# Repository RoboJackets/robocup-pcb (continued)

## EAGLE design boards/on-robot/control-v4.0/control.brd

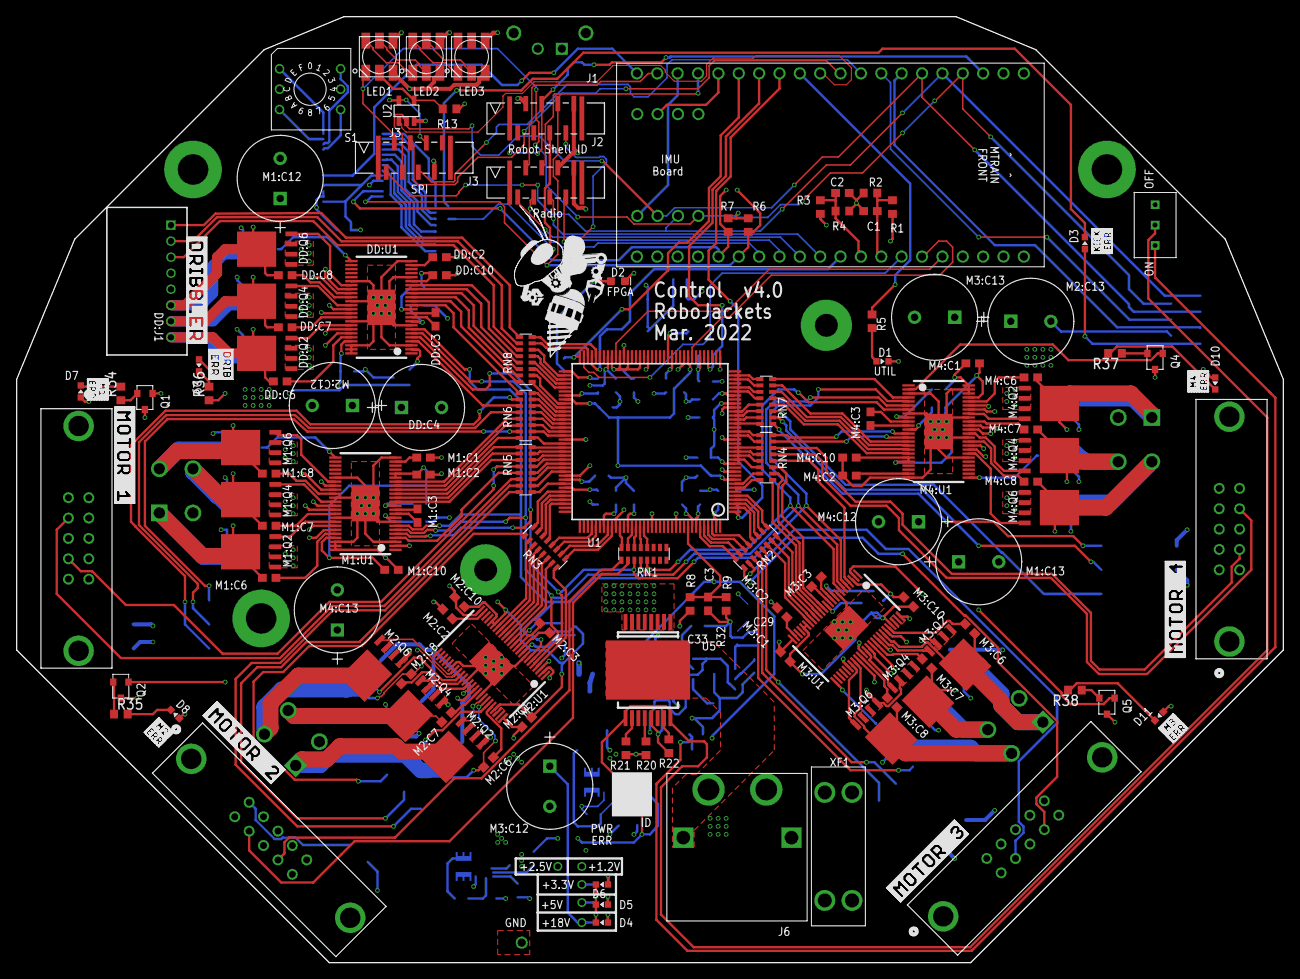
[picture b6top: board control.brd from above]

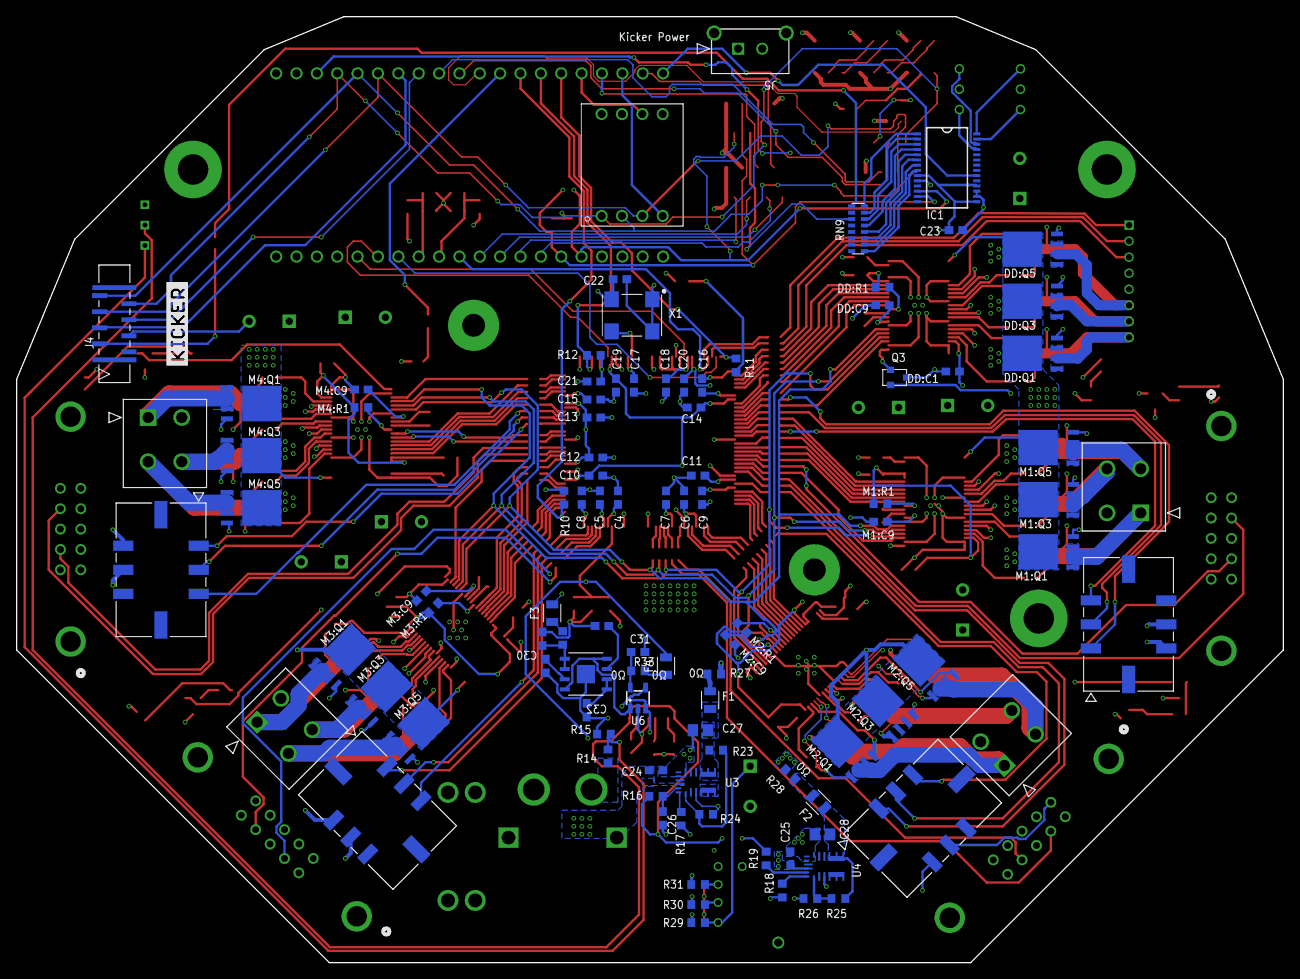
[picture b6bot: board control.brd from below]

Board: 6 copper layers, 158.0 x 118.0 mm, 238 parts (100 on the bottom side), 312 nets.

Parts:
C1: 0.1uF 50V; C0603
C2, C3, C4, C5, C6, C7, C8, C9, C10, C11, C12, C13, C14, C15, C16, C17, C18, C19, C20, C21, C22, C23: 0.1uF; C0603
C24, C25: GRM188R6YA106MA73D; C0603
C26: 2.2uF 50V; C0603
C27, C28: 22uF 16V; C0805
C29: 10uF; C0603
C30, C31, C32, C33: 1uF; C0603
D1: BLUE; CHIP-LED0603
D2: BLUE; LED-0603
D3, D7, D8, D9, D10, D11: RED; CHIP-LED0603
D4, D5, D6: GREEN; CHIP-LED0603
DD:C1, DD:C2: 1uF; C0603
DD:C3: 0.022uF 50V; C0603
DD:C4: ECA-1HHG221; CAP_PAN_10X12.5
DD:C6, DD:C7, DD:C8, DD:C10: 0.1uF 50V; C0603
DD:C9: 2.2uF 50V; C0603
DD:J1: 8-PIN_2MM-H; 2MM-8-H
DD:Q1, DD:Q2, DD:Q3, DD:Q4, DD:Q5, DD:Q6: IRFH7545; PQFN_5X6_E
DD:R1: 10k; R0603
DD:U1: DRV8303DCA; TSSOP-48_PAD
F1, F2, F3, F4: 0805L200SLTHYR; FUSC2113X75
IC1: MCP23017-E/SS; SSOP-28
J1, J2, J3, J4: SFW8S-2STE1LF; CON8_1X8_UB_SFW_JAE
J5: 436500217; CON_436500217_MOL
J6: XT60PW-MAMASS; XT60PW-M
KIT1: MTRAIN; MTRAIN-KIT
KIT2: IMU
LED1, LED2, LED3: APA102C-5050; APA102_5050
M1:C1, M1:C2, M2:C1, M2:C2, M3:C1, M3:C2, M4:C1, M4:C2: 1uF; C0603
M1:C3, M2:C3, M3:C3, M4:C3: 0.022uF 50V; C0603
M1:C6, M1:C7, M1:C8, M1:C10, M2:C6, M2:C7, M2:C8, M2:C10, M3:C6, M3:C7, M3:C8, M3:C10, M4:C6, M4:C7, M4:C8, M4:C10: 0.1uF 50V; C0603
M1:C9, M2:C9, M3:C9, M4:C9: 2.2uF 50V; C0603
M1:C12, M1:C13, M2:C12, M2:C13, M3:C12, M3:C13, M4:C12, M4:C13: ECA-1HHG221; CAP_PAN_10X12.5
M1:J1, M2:J1, M3:J1, M4:J1: 430450618; CON_430450618_MOL
M1:J2, M2:J2, M3:J2, M4:J2: 39288040; CON_39288040
M1:Q1, M1:Q2, M1:Q3, M1:Q4, M1:Q5, M1:Q6, M2:Q1, M2:Q2, M2:Q3, M2:Q4, M2:Q5, M2:Q6, M3:Q1, M3:Q2, M3:Q3, M3:Q4, M3:Q5, M3:Q6, M4:Q1, M4:Q2, M4:Q3, M4:Q4, M4:Q5, M4:Q6: IRFH7545; PQFN_5X6_E
M1:R1, M2:R1, M3:R1, M4:R1: 10k; R0603
M1:U1, M2:U1, M3:U1, M4:U1: DRV8303DCA; TSSOP-48_PAD
M1:U2, M2:U2, M3:U2, M4:U2: N3793-6303RB; N3793-6303RB_3MM
Q1, Q2, Q3, Q4, Q5: PJA3439_R1_00001; SOT-23
R1: 68k 1%; R0603
R2, R3, R4: 10k 1%; R0603
R5, R11: 270; R0603
R6, R7, R10, R12: 4.7k; R0603
R8: 68k; R0603
R9, R20: 10k; R0603
R13: 50k; R0603
R14: 270k; R0603
R15: 100k; R0603
R16, R19: 150k; R0603
R17: 43.2k; R0603
R18: 29.4k; R0603
R21, R22, R29, R30, R31: 1k; R0603
R23, R25: 160k 1%; R0603
R24: 30.1k 1%; R0603
R26: 51.0k 1%; R0603
R27, R28, R32, R33: 0; R0603
R34, R35, R36, R37, R38: 330; R0603
RN1, RN2, RN3, RN4, RN5, RN6, RN7, RN8, RN9: 330; RA-8_2506
S1: 94HCB16T; HEX
S2: TT11EGPC1
U1: XC3S250E-4TQG144C; TQFP144
U2: SN74AHC1G125; SOT-23-5
U3, U4: MPM3620GQV-P
U5: VND5E006ASPTR-E; POWERSO-16
U6: MCP1824T-2502E/OT; SOT-23-5
U7: ADP7158ARDZ-1.2-R7ADP7158ARDZ-1.2-R7_ADI-L; ADP7158ARDZ-1.2-R7_ADI-L
U$1: DRIBBLER
U$2: ERR-KICK
U$3: ERR-DRIB
U$4: ROBOBUZZ_1.0X2
U$5: ERR-M4
U$6: ERR-M1
U$7: MOTOR-1
U$8: MOTOR-4
U$9: MOTOR-2
U$10: ERR-M3
U$11: ERR-M2
U$12: MOTOR-3
U$100: KICKER
X1: ASV-18.432MHZ-EJ-T; ASV
XF1: 30A; 3557-2

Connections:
5V-LED: D5.A, R30.2
5V-LED1: D6.A, R31.2
18.5V-LED: D4.A, R29.1
!CS!-DOT: KIT1.P$11, U2.1
!CS!-FPGA: KIT1.P$31, U1.69
!CS!-ICM: KIT1.P$18, KIT2.4
!CS!-IR: J3.4, KIT1.P$10
!CS!-KICK: J4.5, KIT1.P$8
!CS!-RAD0: J2.4, KIT1.P$17
!RST!-I2C: J1.5, RN9.11
!RST!-IR: J3.5, KIT1.P$9
!RST!-KICK: J4.4, KIT1.P$7
!RST!-RADIO: J2.2, KIT1.P$19
+1.2V: C6.1, C10.1, C14.1, C19.1, F3.2, U1.9, U1.45, U1.80, U1.115
+1.2V-PRE: C29.1, R32.1, U7.1, U7.2
+2.5V: C4.1, C9.1, C15.1, C20.1, F4.2, R10.2, U1.30, U1.65, U1.102, U1.137
+2.5V-PRE: C31.1, R33.1, U6.5
+3.3V: C5.1, C7.1, C8.1, C11.1, C12.1, C13.1, C16.1, C17.1, C18.1, C21.1, C22.1, C23.1, D3.A, D7.A, D8.A, D9.A, D10.A, D11.A, DD:C1.1, DD:C10.1, DD:R1.1, DD:U1.19, DD:U1.45, IC1.9, IC1.15, IC1.18, J3.6, J4.2, KIT2.8, R6.2, R7.2, R12.1, R28.2, R31.1, U1.13, U1.28, U1.42, U1.49, U1.57, U1.60, U1.62, U1.64, U1.79, U1.100, U1.121, U1.138, U1.143, U2.5, U6.1, U6.3, U7.4, U7.8, X1.1, X1.4
+3.3V-FUSE: C28.1, F2.1, R25.2, U4.789
+5V: DD:J1.5, J1.8, J2.6, KIT1.VIN, LED1.1, LED2.1, LED3.1, M1:J1.5, M1:U2.9, M2:J1.5, M2:U2.9, M3:J1.5, M3:U2.9, M4:J1.5, M4:U2.9, R3.1, R27.2, R30.1
+5V-FUSE: C27.1, F1.1, R23.2, U3.789
+18.5V: C24.1, C25.1, DD:C4.1, DD:Q1.5678, DD:Q3.5678, DD:Q5.5678, DD:U1.25, M1:C12.1, M1:C13.1, M1:Q1.5678, M1:Q3.5678, M1:Q5.5678, M1:U1.25, M2:C12.1, M2:C13.1, M2:Q1.5678, M2:Q3.5678, M2:Q5.5678, M2:U1.25, M3:C12.1, M3:C13.1, M3:Q1.5678, M3:Q3.5678, M3:Q5.5678, M3:U1.25, M4:C12.1, M4:C13.1, M4:Q1.5678, M4:Q3.5678, M4:Q5.5678, M4:U1.25, R1.1, R8.1, R29.2, U3.16, U4.16, XF1.3, XF1.4
AAM: R17.2, U3.18
AAM1: R18.2, U4.18
BATT-FPGA: C3.1, R8.2, R9.1, U1.136
BYP: C30.1, U7.3
CS1: R21.2, U5.10
CS2: R22.2, U5.15
CS-DIS: R20.2, U5.12
DD-!CS: DD:U1.4, RN6.11
DD-!FAULT!: DD:U1.2, Q3.1
DD-A-H: DD:U1.13, RN6.9
DD-A-L: DD:U1.14, RN8.16
DD-B-H: DD:U1.15, RN8.15
DD-B-L: DD:U1.16, RN8.14
DD-C-H: DD:U1.17, RN8.13
DD-C-L: DD:U1.18, RN8.12
DD-H1: DD:J1.3, RN8.11
DD-H2: DD:J1.2, RN8.10
DD-H3: DD:J1.1, RN8.9
DD:AVDD: DD:C2.1, DD:U1.23
DD:BST-A: DD:C6.1, DD:U1.44
DD:BST-B: DD:C7.1, DD:U1.39
DD:BST-C: DD:C8.1, DD:U1.34
DD:CP1: DD:C3.1, DD:U1.10
DD:CP2: DD:C3.2, DD:U1.11
DD:EN-GATE: DD:R1.2, DD:U1.12
DD:GH-A: DD:Q1.4, DD:U1.43
DD:GH-B: DD:Q3.4, DD:U1.38
DD:GH-C: DD:Q5.4, DD:U1.33
DD:GL-A: DD:Q2.4, DD:U1.41
DD:GL-B: DD:Q4.4, DD:U1.36
DD:GL-C: DD:Q6.4, DD:U1.31
DD:GVDD: DD:C9.1, DD:U1.9
DD:PHASE-A: DD:C6.2, DD:J1.8, DD:Q1.1, DD:Q1.2, DD:Q1.3, DD:Q2.5678, DD:U1.42
DD:PHASE-B: DD:C7.2, DD:J1.7, DD:Q3.1, DD:Q3.2, DD:Q3.3, DD:Q4.5678, DD:U1.37
DD:PHASE-C: DD:C8.2, DD:J1.6, DD:Q5.1, DD:Q5.2, DD:Q5.3, DD:Q6.5678, DD:U1.32
DOT-CLK-1: LED1.5, R13.2, U2.4
DOT-CLK-1-2: LED1.2, LED2.5
DOT-CLK-2-3: LED2.2, LED3.5
DOT-MOSI-1-2: LED1.3, LED2.4
DOT-MOSI-2-3: LED2.3, LED3.4
EN: C26.1, R16.2, U3.17
EN1: R19.2, U4.17
EN-PWR: R16.1, R19.1, S2.3, U5.9, U5.16
EN-PWR-PRE: R14.1, R15.2, S2.2
EXTRA-IND: KIT1.P$12, R5.1
FB: R23.1, R24.2, U3.1
FB1: R25.1, R26.2, U4.1
FPGA-CLK: U1.50, X1.3
FPGA-DONE: KIT1.P$15, R11.1, U1.72
FPGA-INIT: KIT1.P$14, R12.2, U1.40
FPGA-PROG: KIT1.P$13, R10.1, U1.1
GND: C1.2, C2.2, C3.2, C4.2, C5.2, C6.2, C7.2, C8.2, C9.2, C10.2, C11.2, C12.2, C13.2, C14.2, C15.2, C16.2, C17.2, C18.2, C19.2, C20.2, C21.2, C22.2, C23.2, C24.2, C25.2, C26.2, C27.2, C28.2, C29.2, C30.2, C31.2, C32.2, C33.2, D1.C, D2.C, D4.C, D5.C, D6.C, DD:C1.2, DD:C2.2, DD:C4.2, DD:C9.2, DD:C10.2, DD:J1.4, DD:Q2.1, DD:Q2.2, DD:Q2.3, DD:Q4.1, DD:Q4.2, DD:Q4.3, DD:Q6.1, DD:Q6.2, DD:Q6.3, DD:U1.3, DD:U1.8, DD:U1.20, DD:U1.24, DD:U1.30, DD:U1.35, DD:U1.40, DD:U1.46, DD:U1.47, DD:U1.48, DD:U1.PAD, IC1.10, IC1.16, IC1.17, J1.2, J2.8, J3.7, J4.3, J5.2, J6.P$1, J6.P$3, KIT1.GND, KIT2.5, LED1.6, LED2.6, LED3.6, M1:C1.2, M1:C2.2, M1:C9.2, M1:C10.2, M1:C12.2, M1:C13.2, M1:J1.4, M1:Q2.1, M1:Q2.2, M1:Q2.3, M1:Q4.1, M1:Q4.2, M1:Q4.3, M1:Q6.1, M1:Q6.2, M1:Q6.3, M1:U1.3, M1:U1.8, M1:U1.24, M1:U1.30, M1:U1.35, M1:U1.40, M1:U1.46, M1:U1.47, M1:U1.48, M1:U1.PAD, M1:U2.7, M2:C1.2, M2:C2.2, M2:C9.2, M2:C10.2, M2:C12.2, M2:C13.2, M2:J1.4, M2:Q2.1, M2:Q2.2, M2:Q2.3, M2:Q4.1, M2:Q4.2, M2:Q4.3, M2:Q6.1, M2:Q6.2, M2:Q6.3, M2:U1.3, M2:U1.8, M2:U1.24, M2:U1.30, M2:U1.35, M2:U1.40, M2:U1.46, M2:U1.47, M2:U1.48, M2:U1.PAD, M2:U2.7, M3:C1.2, M3:C2.2, M3:C9.2, M3:C10.2, M3:C12.2, M3:C13.2, M3:J1.4, M3:Q2.1, M3:Q2.2, M3:Q2.3, M3:Q4.1, M3:Q4.2, M3:Q4.3, M3:Q6.1, M3:Q6.2, M3:Q6.3, M3:U1.3, M3:U1.8, M3:U1.24, M3:U1.30, M3:U1.35, M3:U1.40, M3:U1.46, M3:U1.47, M3:U1.48, M3:U1.PAD, M3:U2.7, M4:C1.2, M4:C2.2, M4:C9.2, M4:C10.2, M4:C12.2, M4:C13.2, M4:J1.4, M4:Q2.1, M4:Q2.2, M4:Q2.3, M4:Q4.1, M4:Q4.2, M4:Q4.3, M4:Q6.1, M4:Q6.2, M4:Q6.3, M4:U1.3, M4:U1.8, M4:U1.24, M4:U1.30, M4:U1.35, M4:U1.40, M4:U1.46, M4:U1.47, M4:U1.48, M4:U1.PAD, M4:U2.7, Q1.3, Q2.3, Q3.3, Q4.3, Q5.3, R2.2, R4.2, R9.2, R13.1, R15.1, R17.1, R18.1, R20.1, R21.1, R22.1, R24.1, R26.1, S1.C1, S1.C2, S2.1, U1.11, U1.19, U1.27, U1.37, U1.46, U1.55, U1.61, U1.73, U1.90, U1.99, U1.118, U1.127, U1.133, U2.3, U3.3, U3.12, U3.13, U3.14, U4.3, U4.12, U4.13, U4.14, U5.13, U6.2, U7.EPAD, X1.2
GPB0: IC1.1, RN9.8
GPB1: IC1.2, RN9.7
GPB2: IC1.3, RN9.6
GPB3: IC1.4, RN9.5
GPB4: IC1.5, RN9.4
GPB5: IC1.6, RN9.3
GPB6: IC1.7, RN9.2
GPB7: IC1.8, RN9.1
HEX-0: IC1.28, S1.1
HEX-1: IC1.25, S1.2
HEX-2: IC1.27, S1.4
HEX-3: IC1.26, S1.8
INT-I2C: J1.4, KIT1.P$3
INT-ICM: KIT1.P$16, KIT2.6
INT-IO: IC1.20, KIT1.P$20
INT-RAD0: J2.5, KIT1.P$30
LED-DD: D9.C, R36.2
LED-KICK: D3.C, RN9.9
LED-M1: D7.C, R34.2
LED-M2: D8.C, R35.2
LED-M3: D11.C, R38.2
LED-M4: D10.C, R37.2
M1-!CS: M1:U1.4, RN5.13
M1-!FAULT!: M1:U1.2, Q1.1
M1-A-H: M1:U1.15, RN5.9
M1-A-L: M1:U1.16, RN6.16
M1-B-H: M1:U1.13, RN5.11
M1-B-L: M1:U1.14, RN5.10
M1-C-H: M1:U1.17, RN6.14
M1-C-L: M1:U1.18, RN6.13
M1-ENC-A: M1:U2.8, RN5.14
M1-ENC-B: M1:U2.4, RN5.12
M1-H1: M1:J1.1, RN6.10
M1-H2: M1:J1.2, RN6.12
M1-H3: M1:J1.3, RN6.15
M1:+3.3V: M1:C1.1, M1:C10.1, M1:R1.1, M1:U1.19, M1:U1.20, M1:U1.45
M1:AVDD: M1:C2.1, M1:U1.23
M1:BST-A: M1:C6.1, M1:U1.44
M1:BST-B: M1:C7.1, M1:U1.39
M1:BST-C: M1:C8.1, M1:U1.34
M1:CP1: M1:C3.1, M1:U1.10
M1:CP2: M1:C3.2, M1:U1.11
M1:EN-GATE: M1:R1.2, M1:U1.12
M1:GH-A: M1:Q1.4, M1:U1.43
M1:GH-B: M1:Q3.4, M1:U1.38
M1:GH-C: M1:Q5.4, M1:U1.33
M1:GL-A: M1:Q2.4, M1:U1.41
M1:GL-B: M1:Q4.4, M1:U1.36
M1:GL-C: M1:Q6.4, M1:U1.31
M1:GVDD: M1:C9.1, M1:U1.9
M1:PHASE-A: M1:C7.2, M1:J2.4, M1:Q3.1, M1:Q3.2, M1:Q3.3, M1:Q4.5678, M1:U1.37
M1:PHASE-B: M1:C6.2, M1:J2.1, M1:Q1.1, M1:Q1.2, M1:Q1.3, M1:Q2.5678, M1:U1.42
M1:PHASE-C: M1:C8.2, M1:J2.3, M1:Q5.1, M1:Q5.2, M1:Q5.3, M1:Q6.5678, M1:U1.32
M2-!CS: M2:U1.4, RN3.16
M2-!FAULT!: M2:U1.2, Q2.1
M2-A-H: M2:U1.15, RN3.13
M2-A-L: M2:U1.16, RN3.12
M2-B-H: M2:U1.13, RN3.15
M2-B-L: M2:U1.14, RN3.14
M2-C-H: M2:U1.17, RN3.11
M2-C-L: M2:U1.18, RN3.10
M2-ENC-A: M2:U2.8, RN1.10
M2-ENC-B: M2:U2.4, RN1.9
M2-H1: M2:J1.1, RN5.15
M2-H2: M2:J1.2, RN5.16
M2-H3: M2:J1.3, RN3.9
M2:+3.3V: M2:C1.1, M2:C10.1, M2:R1.1, M2:U1.19, M2:U1.20, M2:U1.45
M2:AVDD: M2:C2.1, M2:U1.23
M2:BST-A: M2:C6.1, M2:U1.44
M2:BST-B: M2:C7.1, M2:U1.39
M2:BST-C: M2:C8.1, M2:U1.34
M2:CP1: M2:C3.1, M2:U1.10
M2:CP2: M2:C3.2, M2:U1.11
M2:EN-GATE: M2:R1.2, M2:U1.12
M2:GH-A: M2:Q1.4, M2:U1.43
M2:GH-B: M2:Q3.4, M2:U1.38
M2:GH-C: M2:Q5.4, M2:U1.33
M2:GL-A: M2:Q2.4, M2:U1.41
M2:GL-B: M2:Q4.4, M2:U1.36
M2:GL-C: M2:Q6.4, M2:U1.31
M2:GVDD: M2:C9.1, M2:U1.9
M2:PHASE-A: M2:C7.2, M2:J2.4, M2:Q3.1, M2:Q3.2, M2:Q3.3, M2:Q4.5678, M2:U1.37
M2:PHASE-B: M2:C6.2, M2:J2.1, M2:Q1.1, M2:Q1.2, M2:Q1.3, M2:Q2.5678, M2:U1.42
M2:PHASE-C: M2:C8.2, M2:J2.3, M2:Q5.1, M2:Q5.2, M2:Q5.3, M2:Q6.5678, M2:U1.32
M3-!CS: M3:U1.4, RN4.12
M3-!FAULT!: M3:U1.2, Q5.1
M3-A-H: M3:U1.15, RN4.9
M3-A-L: M3:U1.16, RN2.16
M3-B-H: M3:U1.13, RN4.11
M3-B-L: M3:U1.14, RN4.10
M3-C-H: M3:U1.17, RN2.15
M3-C-L: M3:U1.18, RN2.14
M3-ENC-A: M3:U2.8, RN2.10
M3-ENC-B: M3:U2.4, RN2.9
M3-H1: M3:J1.1, RN2.11
M3-H2: M3:J1.2, RN2.12
M3-H3: M3:J1.3, RN2.13
M3:+3.3V: M3:C1.1, M3:C10.1, M3:R1.1, M3:U1.19, M3:U1.20, M3:U1.45
M3:AVDD: M3:C2.1, M3:U1.23
M3:BST-A: M3:C6.1, M3:U1.44
M3:BST-B: M3:C7.1, M3:U1.39
M3:BST-C: M3:C8.1, M3:U1.34
M3:CP1: M3:C3.1, M3:U1.10
M3:CP2: M3:C3.2, M3:U1.11
M3:EN-GATE: M3:R1.2, M3:U1.12
M3:GH-A: M3:Q1.4, M3:U1.43
M3:GH-B: M3:Q3.4, M3:U1.38
M3:GH-C: M3:Q5.4, M3:U1.33
M3:GL-A: M3:Q2.4, M3:U1.41
M3:GL-B: M3:Q4.4, M3:U1.36
M3:GL-C: M3:Q6.4, M3:U1.31
M3:GVDD: M3:C9.1, M3:U1.9
M3:PHASE-A: M3:C7.2, M3:J2.4, M3:Q3.1, M3:Q3.2, M3:Q3.3, M3:Q4.5678, M3:U1.37
M3:PHASE-B: M3:C6.2, M3:J2.1, M3:Q1.1, M3:Q1.2, M3:Q1.3, M3:Q2.5678, M3:U1.42
M3:PHASE-C: M3:C8.2, M3:J2.3, M3:Q5.1, M3:Q5.2, M3:Q5.3, M3:Q6.5678, M3:U1.32
M4-!CS: M4:U1.4, RN7.16
M4-!FAULT!: M4:U1.2, Q4.1
M4-A-H: M4:U1.15, RN7.15
M4-A-L: M4:U1.16, RN7.14
M4-B-H: M4:U1.13, RN4.16
M4-B-L: M4:U1.14, RN4.15
M4-C-H: M4:U1.17, RN7.13
M4-C-L: M4:U1.18, RN7.12
M4-ENC-A: M4:U2.8, RN4.14
M4-ENC-B: M4:U2.4, RN4.13
M4-H1: M4:J1.1, RN7.9
M4-H2: M4:J1.2, RN7.10
M4-H3: M4:J1.3, RN7.11
M4:+3.3V: M4:C1.1, M4:C10.1, M4:R1.1, M4:U1.19, M4:U1.20, M4:U1.45
M4:AVDD: M4:C2.1, M4:U1.23
M4:BST-A: M4:C6.1, M4:U1.44
M4:BST-B: M4:C7.1, M4:U1.39
M4:BST-C: M4:C8.1, M4:U1.34
M4:CP1: M4:C3.1, M4:U1.10
M4:CP2: M4:C3.2, M4:U1.11
M4:EN-GATE: M4:R1.2, M4:U1.12
M4:GH-A: M4:Q1.4, M4:U1.43
M4:GH-B: M4:Q3.4, M4:U1.38
M4:GH-C: M4:Q5.4, M4:U1.33
M4:GL-A: M4:Q2.4, M4:U1.41
M4:GL-B: M4:Q4.4, M4:U1.36
M4:GL-C: M4:Q6.4, M4:U1.31
M4:GVDD: M4:C9.1, M4:U1.9
M4:PHASE-A: M4:C7.2, M4:J2.4, M4:Q3.1, M4:Q3.2, M4:Q3.3, M4:Q4.5678, M4:U1.37
M4:PHASE-B: M4:C6.2, M4:J2.1, M4:Q1.1, M4:Q1.2, M4:Q1.3, M4:Q2.5678, M4:U1.42
M4:PHASE-C: M4:C8.2, M4:J2.3, M4:Q5.1, M4:Q5.2, M4:Q5.3, M4:Q6.5678, M4:U1.32
MISO: J3.1, J4.8, KIT1.P$5, KIT2.2
MISO-AUX: DD:U1.6, M1:U1.6, M2:U1.6, M3:U1.6, M4:U1.6, RN1.12
MISO-FPGA: KIT1.P$35, U1.44
MISO-RADIO: J2.7, KIT1.P$28
MOSI: J3.2, J4.7, KIT1.P$4, KIT2.1, LED1.4
MOSI-AUX: DD:U1.5, M1:U1.5, M2:U1.5, M3:U1.5, M4:U1.5, RN1.11
MOSI-FPGA: KIT1.P$36, U1.63
MOSI-RADIO: J2.3, KIT1.P$27
unnamed: F2.2, R28.1
unnamed: F1.2, R27.1
unnamed: F3.1, R32.2
unnamed: F4.1, R33.2
unnamed: D2.A, R11.2
unnamed: D1.A, R5.2
R-D-DD: Q3.2, R36.1
R-D-M1: Q1.2, R34.1
R-D-M2: Q2.2, R35.1
R-D-M3: Q5.2, R38.1
R-D-M4: Q4.2, R37.1
R-P1: RN8.1, U1.82
R-P2: RN8.2, U1.81
R-P3: RN8.3, U1.77
R-P4: RN8.4, U1.76
R-P5: RN8.5, U1.75
R-P6: RN8.6, U1.74
R-P7: RN8.7, U1.70
R-P8: RN8.8, U1.68
R-P9: RN6.1, U1.91
R-P10: RN6.2, U1.89
R-P11: RN6.3, U1.88
R-P12: RN6.4, U1.87
R-P13: RN6.5, U1.86
R-P14: RN6.6, U1.85
R-P15: RN6.7, U1.84
R-P16: RN6.8, U1.83
R-P17: RN5.1, U1.101
R-P18: RN5.2, U1.98
R-P19: RN5.3, U1.97
R-P20: RN5.4, U1.96
R-P21: RN5.5, U1.95
R-P22: RN5.6, U1.94
R-P23: RN5.7, U1.93
R-P24: RN5.8, U1.92
R-P25: RN3.1, U1.117
R-P26: RN3.2, U1.116
R-P27: RN3.3, U1.113
R-P28: RN3.4, U1.112
R-P29: RN3.5, U1.106
R-P30: RN3.6, U1.105
R-P31: RN3.7, U1.104
R-P32: RN3.8, U1.103
R-P36: RN1.4, U1.125
R-P37: RN1.5, U1.124
R-P38: RN1.6, U1.123
R-P39: RN1.7, U1.122
R-P40: RN1.8, U1.119
R-P41: RN2.1, U1.5
R-P42: RN2.2, U1.4
R-P43: RN2.3, U1.3
R-P44: RN2.4, U1.2
R-P45: RN2.5, U1.142
R-P46: RN2.6, U1.141
R-P47: RN2.7, U1.140
R-P48: RN2.8, U1.139
R-P49: RN4.1, U1.21
R-P50: RN4.2, U1.20
R-P51: RN4.3, U1.17
R-P52: RN4.4, U1.16
R-P53: RN4.5, U1.15
R-P54: RN4.6, U1.14
R-P55: RN4.7, U1.8
R-P56: RN4.8, U1.7
R-P57: RN7.1, U1.35
R-P58: RN7.2, U1.34
R-P59: RN7.3, U1.32
R-P60: RN7.4, U1.31
R-P61: RN7.5, U1.26
R-P62: RN7.6, U1.25
R-P63: RN7.7, U1.24
R-P64: RN7.8, U1.23
REF_NET: C32.1, U7.5, U7.6
SCK: J3.3, J4.6, KIT1.P$6, KIT2.3, U2.2
SCK-AUX: DD:U1.7, M1:U1.7, M2:U1.7, M3:U1.7, M4:U1.7, RN1.13
SCK-FPGA: KIT1.P$34, U1.71
SCK-RADIO: J2.1, KIT1.P$29
SCL: IC1.12, J1.7, KIT1.P$25, R7.1
SDA: IC1.13, J1.6, KIT1.P$26, R6.1
SENSE-BATT: C1.1, KIT1.P$33, R1.2, R2.1
SENSE-VIN: C2.1, KIT1.P$32, R3.2, R4.1
VBATT: J5.1, U5.1, U5.2, U5.3, U5.4, U5.5, U5.6, U5.7, U5.8, XF1.1, XF1.2
VIN: J6.P$2, J6.P$4, R14.2, U5.17
VREG: C33.1, U7.7

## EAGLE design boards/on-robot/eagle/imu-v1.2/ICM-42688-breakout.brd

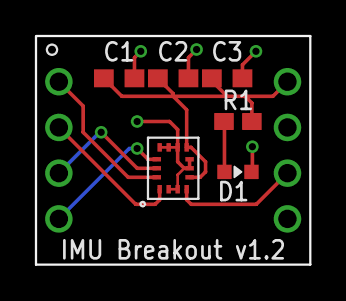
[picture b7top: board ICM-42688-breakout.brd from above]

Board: 2 copper layers, 15.2 x 12.7 mm, 7 parts (0 on the bottom side), 8 nets.

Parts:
C1: 0.01uF; C0603
C2: 0.1uF; C0603
C3: 2.2uF; C0603
D1: GREEN; CHIP-LED0603
KIT1: IMUIMU-KIT; IMU-KIT
R1: 330; R0603W
U3: ICM-42688ICM42688; ICM-442605-2530091

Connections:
!CS!: KIT1.4, U3.P$12
+3.3V: C1.1, C2.1, C3.1, KIT1.8, R1.2, U3.P$5, U3.P$8
CLK: KIT1.3, U3.P$13
GND: C1.2, C2.2, C3.2, D1.C, KIT1.5, U3.P$2, U3.P$3, U3.P$6, U3.P$7, U3.P$9, U3.P$10, U3.P$11
INT: KIT1.6, U3.P$4
MISO: KIT1.2, U3.P$1
MOSI: KIT1.1, U3.P$14
unnamed: D1.A, R1.1
